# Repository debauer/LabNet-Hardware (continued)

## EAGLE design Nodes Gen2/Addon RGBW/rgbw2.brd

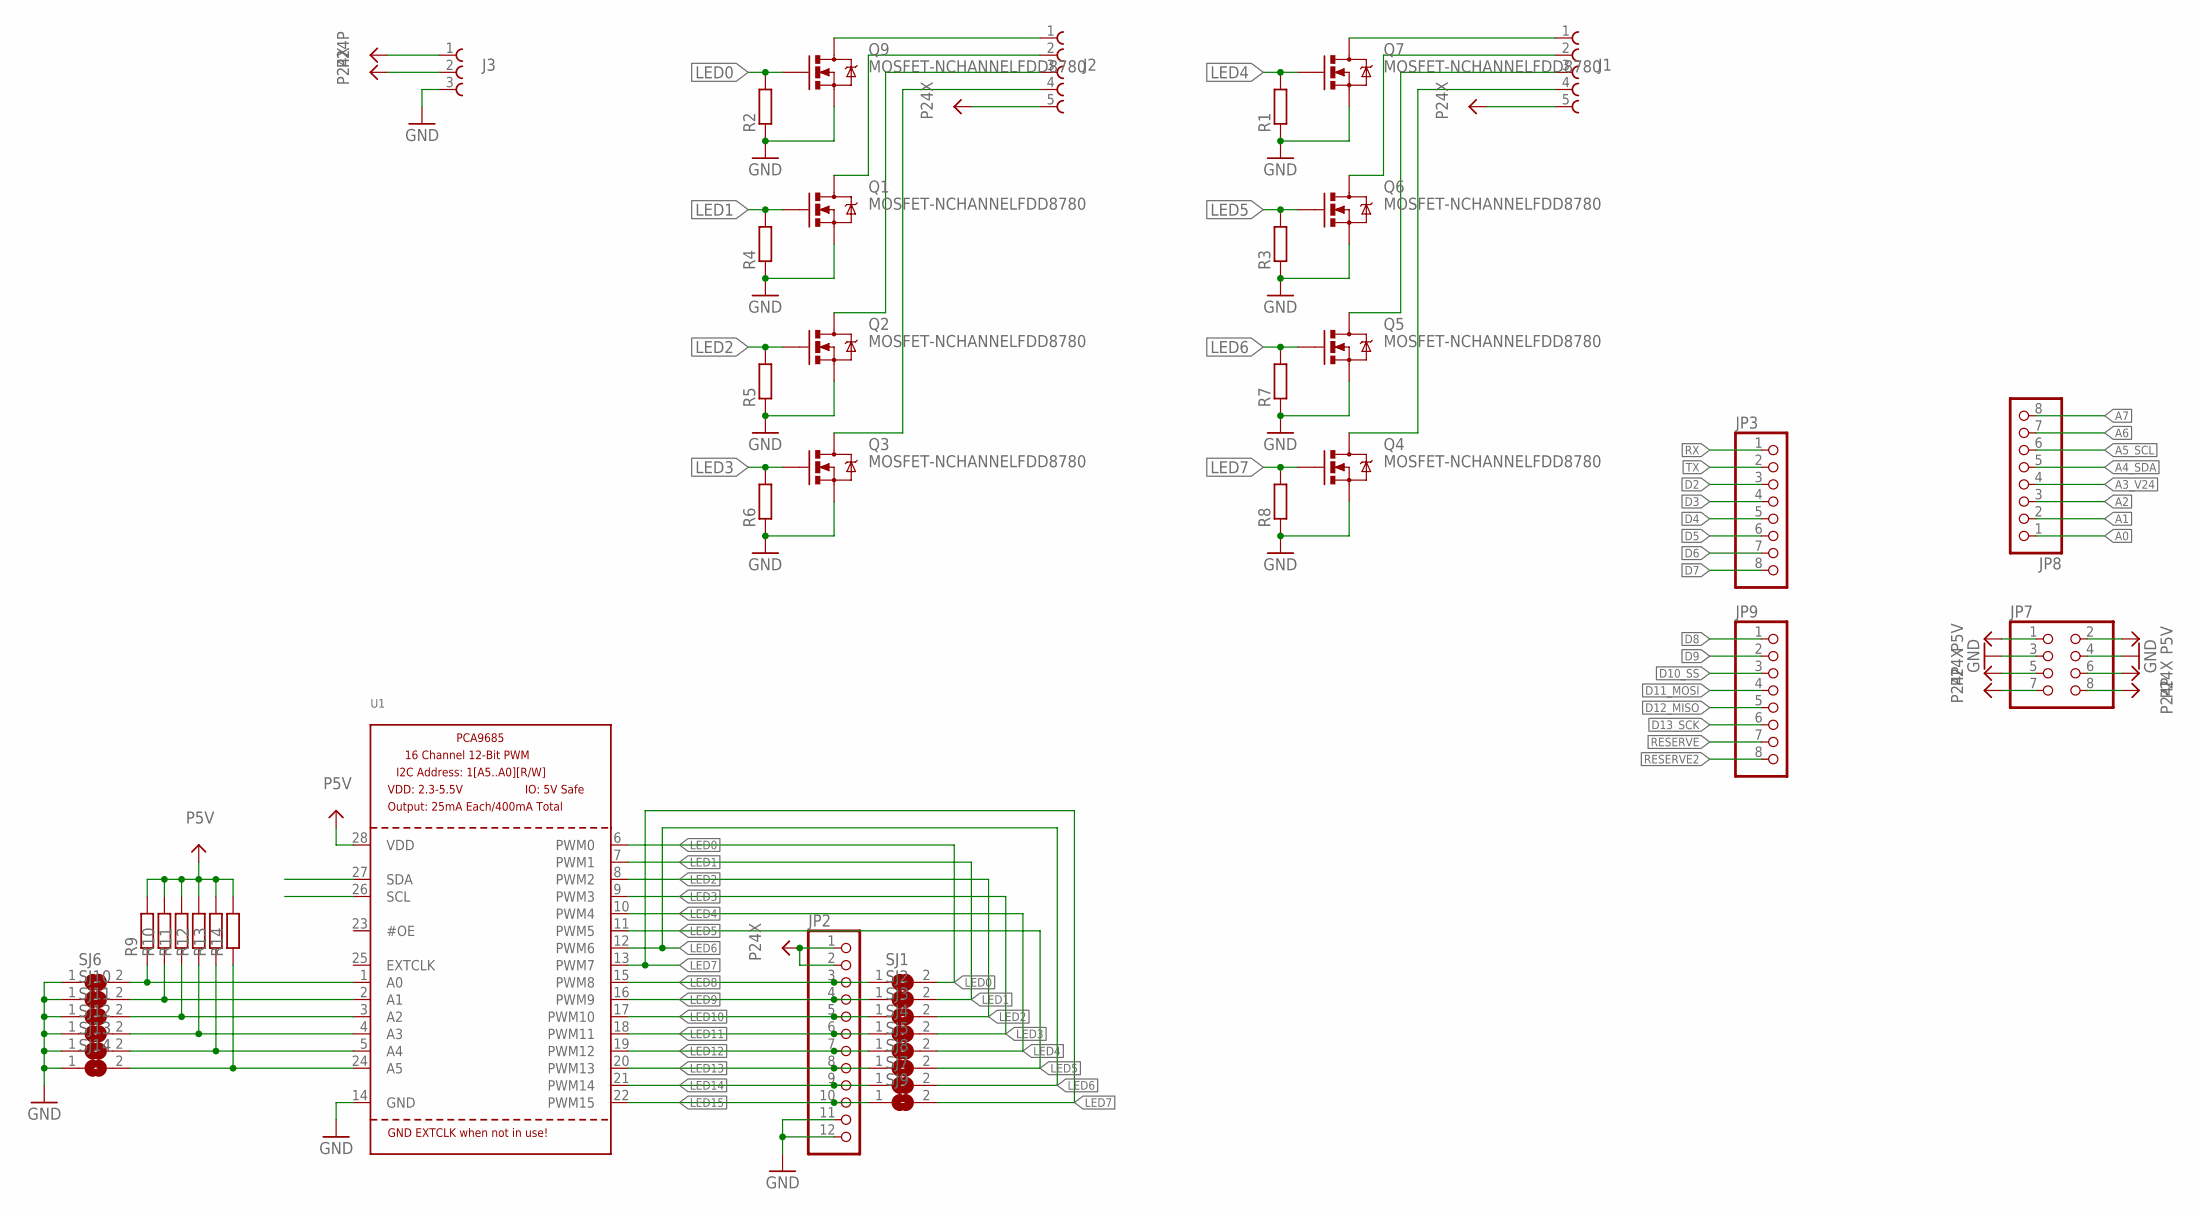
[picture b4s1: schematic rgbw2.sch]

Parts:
J1, J2: 691322310005
J3: 691313510003
JP2: PINHD-1X12; 1X12
JP3, JP8, JP9: PINHD-1X8; 1X08
JP7: PINHD-2X4; 2X04
Q1, Q2, Q3, Q4, Q5, Q6, Q7, Q9: MOSFET-NCHANNELFDD8780; DPAK
R1, R2, R3, R4, R5, R6, R7, R8, R9, R10, R11, R12, R13, R14: R-EU_R0805; R0805
SJ1, SJ2, SJ3, SJ4, SJ5, SJ6, SJ7, SJ8, SJ9, SJ10, SJ11, SJ12, SJ13, SJ14: SJN; SJ
U1: PCA9685; TSSOP28

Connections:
A0: JP8.1
A1: JP8.2
A2: JP8.3
A3_V24: JP8.4
A4_SDA: JP8.5, U1.27 (SDA)
A5_SCL: JP8.6, U1.26 (SCL)
A6: JP8.7
A7: JP8.8
D2: JP3.3
D3: JP3.4
D4: JP3.5
D5: JP3.6
D6: JP3.7
D7: JP3.8
D8: JP9.1
D9: JP9.2
D10_SS: JP9.3
D11_MOSI: JP9.4
D12_MISO: JP9.5
D13_SCK: JP9.6
GND: J3.3, JP2.11, JP2.12, JP7.3, JP7.4, Q1.3 (S), Q2.3 (S), Q3.3 (S), Q4.3 (S), Q5.3 (S), Q6.3 (S), Q7.3 (S), Q9.3 (S), R1.1, R2.1, R3.1, R4.1, R5.1, R6.1, R7.1, R8.1, SJ6.1, SJ10.1, SJ11.1, SJ12.1, SJ13.1, SJ14.1, U1.14 (GND)
LED0: Q9.1 (G), R2.2, SJ1.2, U1.6 (PWM0)
LED1: Q1.1 (G), R4.2, SJ2.2, U1.7 (PWM1)
LED2: Q2.1 (G), R5.2, SJ3.2, U1.8 (PWM2)
LED3: Q3.1 (G), R6.2, SJ4.2, U1.9 (PWM3)
LED4: Q7.1 (G), R1.2, SJ5.2, U1.10 (PWM4)
LED5: Q6.1 (G), R3.2, SJ8.2, U1.11 (PWM5)
LED6: Q5.1 (G), R7.2, SJ7.2, U1.12 (PWM6)
LED7: Q4.1 (G), R8.2, SJ9.2, U1.13 (PWM7)
LED8: JP2.3, SJ1.1, U1.15 (PWM8)
LED9: JP2.4, SJ2.1, U1.16 (PWM9)
LED10: JP2.5, SJ3.1, U1.17 (PWM10)
LED11: JP2.6, SJ4.1, U1.18 (PWM11)
LED12: JP2.7, SJ5.1, U1.19 (PWM12)
LED13: JP2.8, SJ8.1, U1.20 (PWM13)
LED14: JP2.9, SJ7.1, U1.21 (PWM14)
LED15: JP2.10, SJ9.1, U1.22 (PWM15)
unnamed: R9.1, SJ6.2, U1.1 (A0)
unnamed: J2.1, Q9.4 (D)
unnamed: J2.2, Q1.4 (D)
unnamed: J1.3, Q5.4 (D)
unnamed: J2.3, Q2.4 (D)
unnamed: J2.4, Q3.4 (D)
unnamed: J1.4, Q4.4 (D)
unnamed: J1.1, Q7.4 (D)
unnamed: J1.2, Q6.4 (D)
unnamed: R10.1, SJ10.2, U1.2 (A1)
unnamed: R11.1, SJ11.2, U1.3 (A2)
unnamed: R12.1, SJ12.2, U1.4 (A3)
unnamed: R13.1, SJ13.2, U1.5 (A4)
unnamed: R14.1, SJ14.2, U1.24 (A5)
P5V: JP7.1, JP7.2, R9.2, R10.2, R11.2, R12.2, R13.2, R14.2, U1.28 (VDD)
P24P: J3.1, JP7.7, JP7.8
P24X: J1.5, J2.5, J3.2, JP2.1, JP2.2, JP7.5, JP7.6
RESERVE: JP9.7
RESERVE2: JP9.8
RX: JP3.1
TX: JP3.2

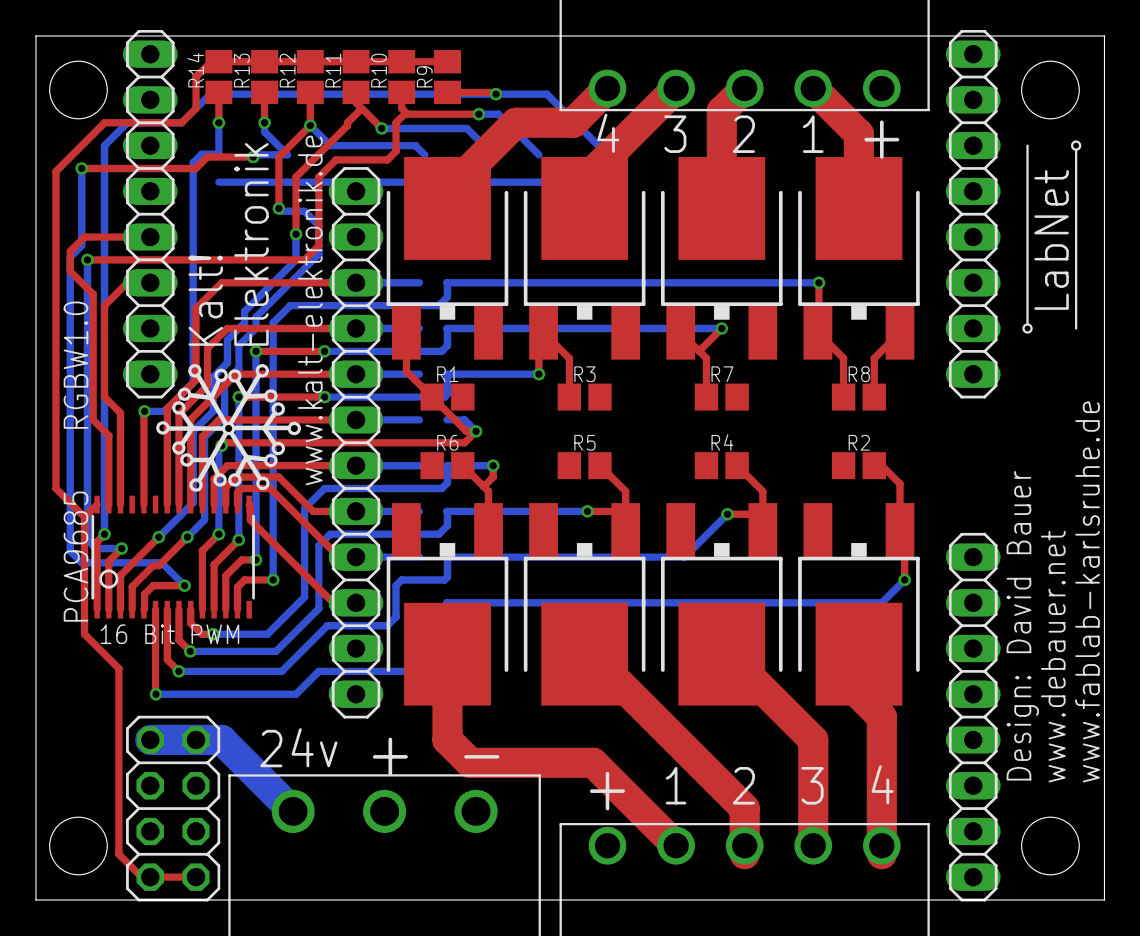
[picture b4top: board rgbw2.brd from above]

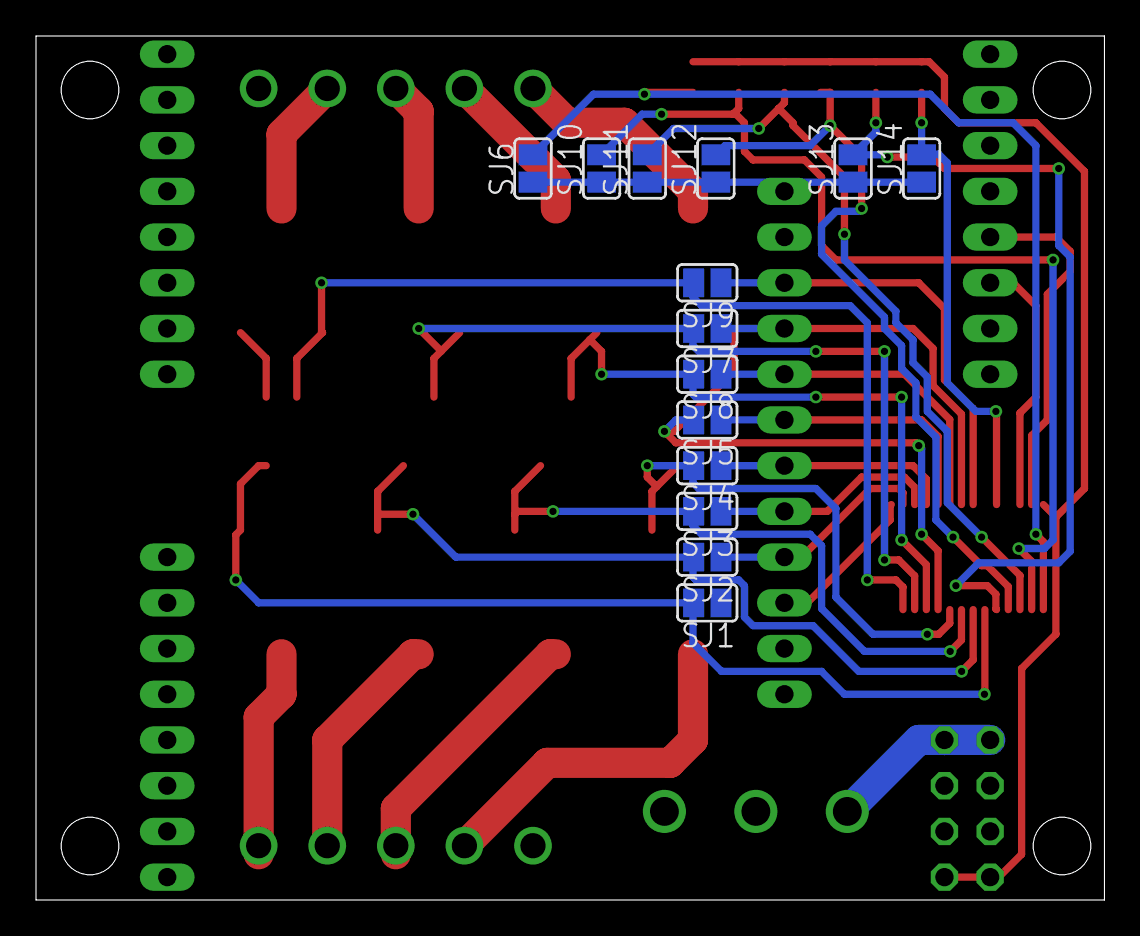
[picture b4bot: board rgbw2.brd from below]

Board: 2 copper layers, 59.4 x 48.0 mm, 47 parts (14 on the bottom side), 36 nets.

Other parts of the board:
U$1: KALT!ELEKTRONIK
U$2: LABNET

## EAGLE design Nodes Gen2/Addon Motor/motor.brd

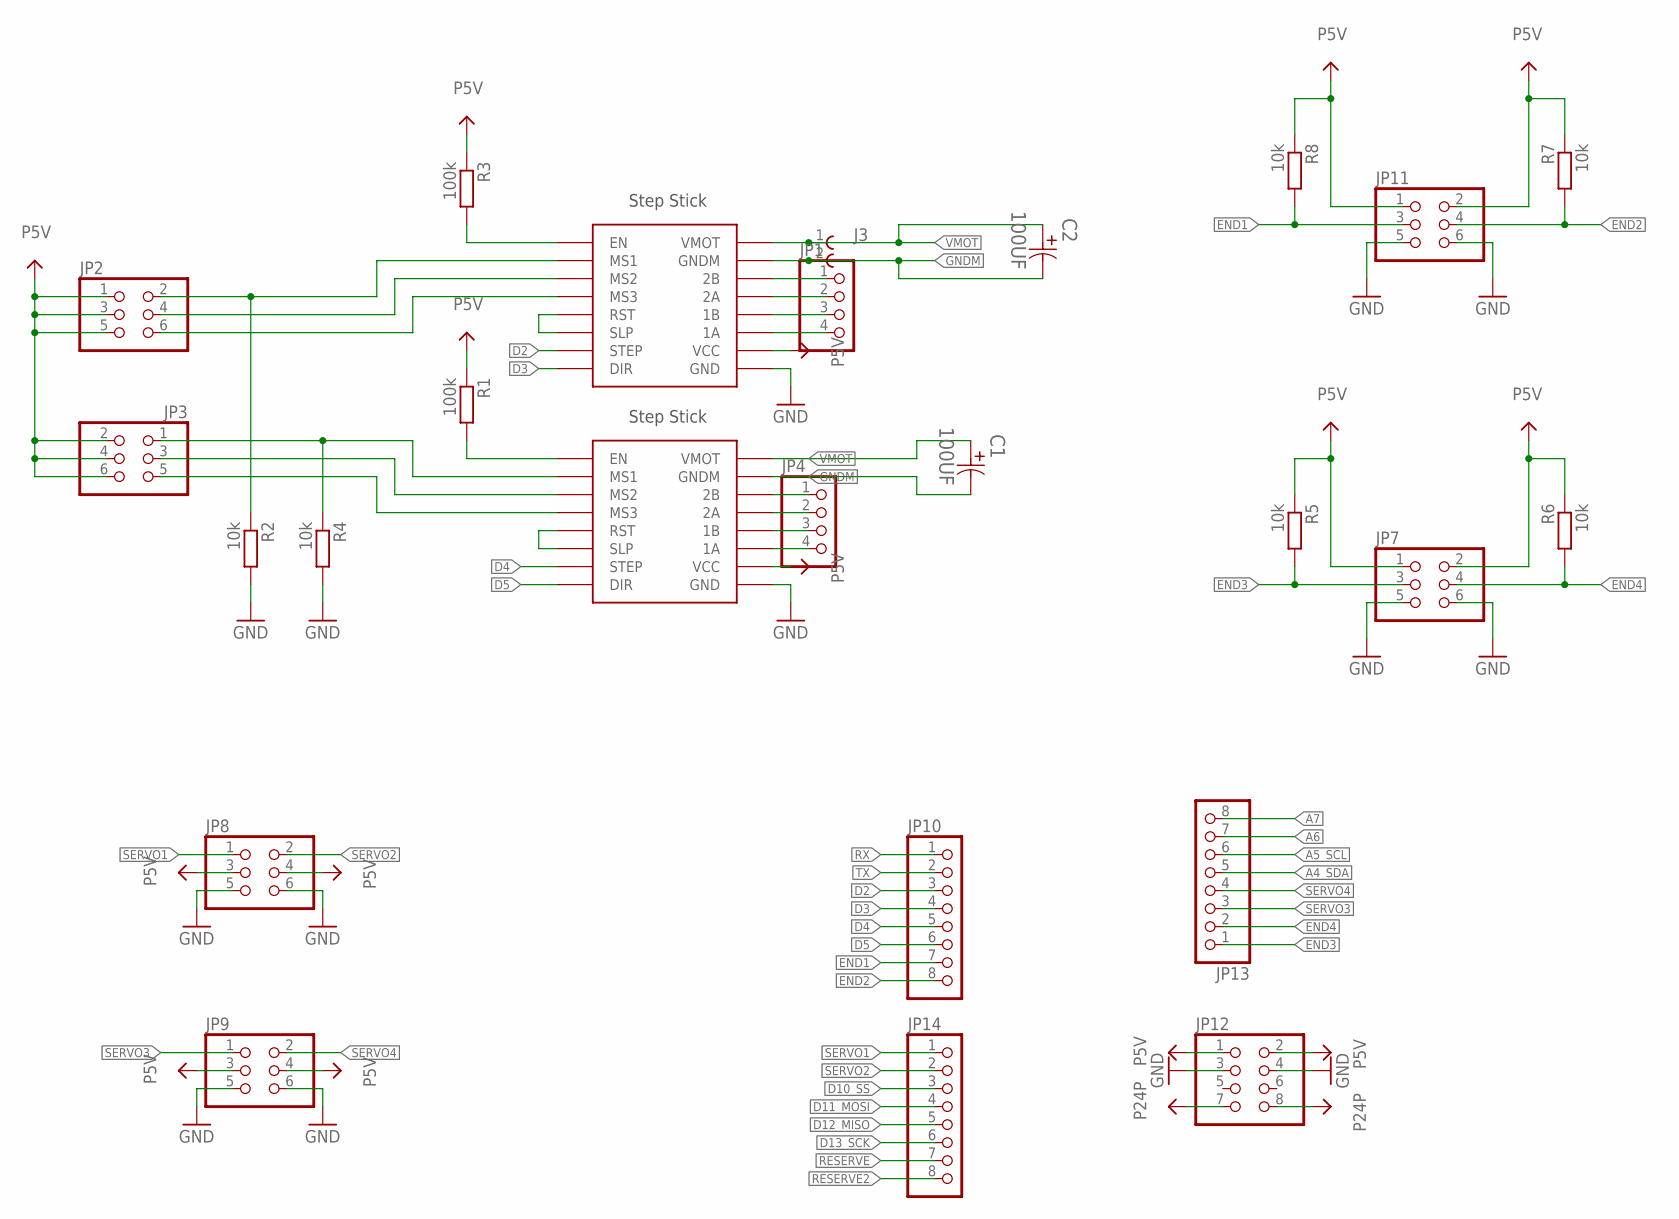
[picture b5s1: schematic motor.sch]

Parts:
C1, C2: 100UF; CAPAE830X1050N
J3: 691312510002
JP1, JP4: PINHD-1X4/90; 1X04/90
JP2, JP3: PINHD-2X3; 2X03
JP7, JP8, JP9, JP11: PINHD-2X3/90; 2X03/90
JP10, JP13, JP14: PINHD-1X8; 1X08
JP12: PINHD-2X4; 2X04
R1, R3: 100k; R0805
R2, R4, R5, R6, R7, R8: 10k; R0805
U$1, U$2: STEP-STICK

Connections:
A4_SDA: JP13.5
A5_SCL: JP13.6
A6: JP13.7
A7: JP13.8
D2: JP10.3, U$2.SPT (STEP)
D3: JP10.4, U$2.DIR
D4: JP10.5, U$1.SPT (STEP)
D5: JP10.6, U$1.DIR
D10_SS: JP14.3
D11_MOSI: JP14.4
D12_MISO: JP14.5
D13_SCK: JP14.6
END1: JP10.7, JP11.3, R8.2
END2: JP10.8, JP11.4, R7.2
END3: JP7.3, JP13.1, R5.2
END4: JP7.4, JP13.2, R6.2
GND: JP7.5, JP7.6, JP8.5, JP8.6, JP9.5, JP9.6, JP11.5, JP11.6, JP12.3, JP12.4, R2.2, R4.2, U$1.GND, U$2.GND
GNDM: C1.2, C2.2, J3.2, U$1.GNDM, U$2.GNDM
unnamed: JP2.2, R2.1, U$2.MS1
unnamed: JP2.4, U$2.MS2
unnamed: JP2.6, U$2.MS3
unnamed: JP3.1, R4.1, U$1.MS1
unnamed: JP3.3, U$1.MS2
unnamed: JP3.5, U$1.MS3
unnamed: R1.2, U$1.EN
unnamed: U$2.RST, U$2.SLP
unnamed: R3.2, U$2.EN
unnamed: U$1.RST, U$1.SLP
unnamed: JP1.4, U$2.1A
unnamed: JP1.3, U$2.1B
unnamed: JP1.2, U$2.2A
unnamed: JP1.1, U$2.2B
unnamed: JP4.1, U$1.2B
unnamed: JP4.2, U$1.2A
unnamed: JP4.3, U$1.1B
unnamed: JP4.4, U$1.1A
P5V: JP2.1, JP2.3, JP2.5, JP3.2, JP3.4, JP3.6, JP7.1, JP7.2, JP8.3, JP8.4, JP9.3, JP9.4, JP11.1, JP11.2, JP12.1, JP12.2, R1.1, R3.1, R5.1, R6.1, R7.1, R8.1, U$1.VCC, U$2.VCC
P24P: JP12.7, JP12.8
RESERVE: JP14.7
RESERVE2: JP14.8
RX: JP10.1
SERVO1: JP8.1, JP14.1
SERVO2: JP8.2, JP14.2
SERVO3: JP9.1, JP13.3
SERVO4: JP9.2, JP13.4
TX: JP10.2
VMOT: C1.1, C2.1, J3.1, U$1.VMOT, U$2.VMOT

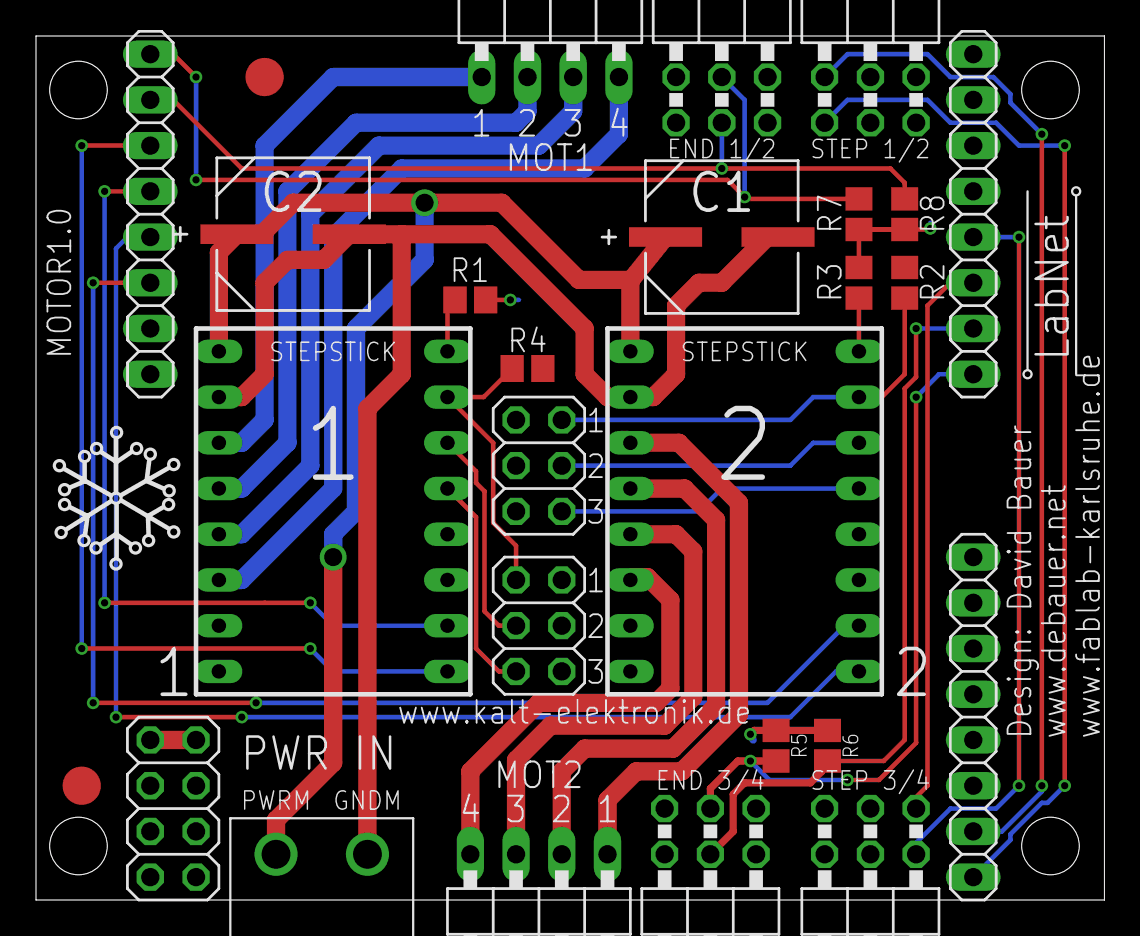
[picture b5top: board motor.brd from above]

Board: 2 copper layers, 59.4 x 48.0 mm, 30 parts (1 on the bottom side), 35 nets.

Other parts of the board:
U$3, U$8: PASSMARK
U$4: SNOW
U$6: KALT!ELEKTRONIK
U$7: LABNET

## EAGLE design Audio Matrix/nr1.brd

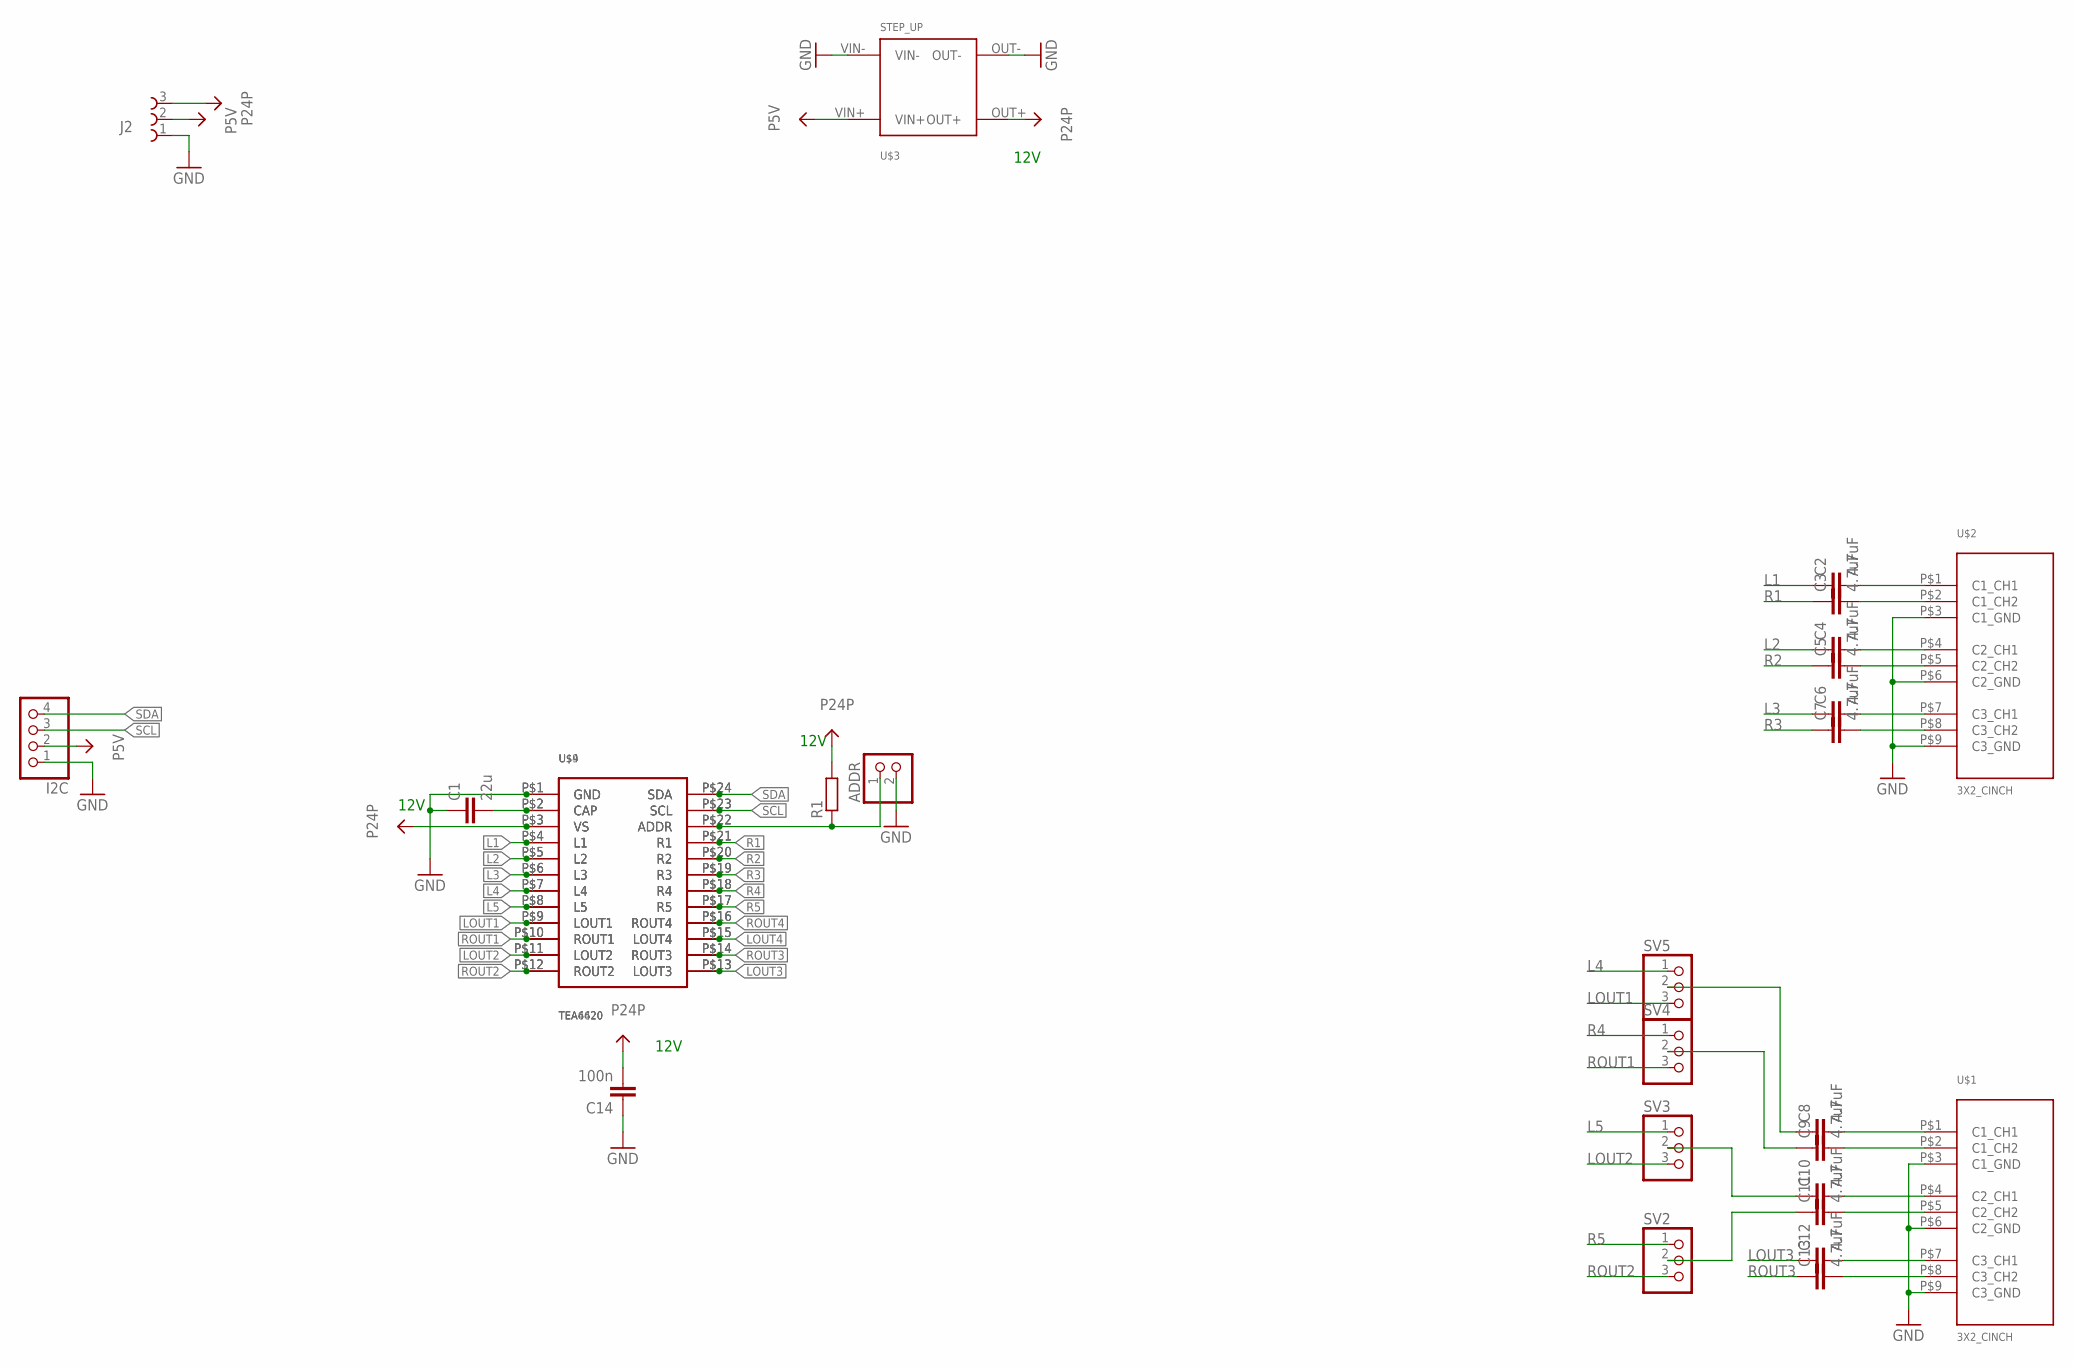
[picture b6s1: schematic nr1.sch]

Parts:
ADDR: PINHD-1X2; 1X02
C1: 22u; C0805
C2, C3, C4, C5, C6, C7, C8, C9, C10, C11, C12, C13: 4.7uF; C0805
C14: 100n; C0805
I2C: PINHD-1X4; 1X04
J2: 691210910003
R1: R-EU_R0805; R0805
SV2, SV3, SV4, SV5: PINHD-1X3; 1X03
U$1, U$2: 3X2_CINCH
U$3: STEP_UP
U$4: TEA4620
U$9: TEA6420; SHRINK24

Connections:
GND: ADDR.2, C1.1, C14.1, I2C.1, J2.1, U$1.P$3 (C1_GND), U$1.P$6 (C2_GND), U$1.P$9 (C3_GND), U$2.P$3 (C1_GND), U$2.P$6 (C2_GND), U$2.P$9 (C3_GND), U$3.OUT-, U$3.VIN-, U$4.P$1 (GND), U$9.P$1 (GND)
L1: C2.1, U$4.P$4 (L1), U$9.P$4 (L1)
L2: C4.1, U$4.P$5 (L2), U$9.P$5 (L2)
L3: C6.1, U$4.P$6 (L3), U$9.P$6 (L3)
L4: SV5.1, U$4.P$7 (L4), U$9.P$7 (L4)
L5: SV3.1, U$4.P$8 (L5), U$9.P$8 (L5)
LOUT1: SV5.3, U$4.P$9 (LOUT1), U$9.P$9 (LOUT1)
LOUT2: SV3.3, U$4.P$11 (LOUT2), U$9.P$11 (LOUT2)
LOUT3: C12.1, U$4.P$13 (LOUT3), U$9.P$13 (LOUT3)
LOUT4: U$4.P$15 (LOUT4), U$9.P$15 (LOUT4)
unnamed: C8.1, SV5.2
unnamed: C9.1, SV4.2
unnamed: ADDR.1, R1.1, U$4.P$22 (ADDR), U$9.P$22 (ADDR)
unnamed: C1.2, U$4.P$2 (CAP), U$9.P$2 (CAP)
unnamed: C10.1, SV3.2
unnamed: C11.1, SV2.2
unnamed: C2.2, U$2.P$1 (C1_CH1)
unnamed: C3.2, U$2.P$2 (C1_CH2)
unnamed: C4.2, U$2.P$4 (C2_CH1)
unnamed: C5.2, U$2.P$5 (C2_CH2)
unnamed: C6.2, U$2.P$7 (C3_CH1)
unnamed: C7.2, U$2.P$8 (C3_CH2)
unnamed: C8.2, U$1.P$1 (C1_CH1)
unnamed: C9.2, U$1.P$2 (C1_CH2)
unnamed: C10.2, U$1.P$4 (C2_CH1)
unnamed: C11.2, U$1.P$5 (C2_CH2)
unnamed: C12.2, U$1.P$7 (C3_CH1)
unnamed: C13.2, U$1.P$8 (C3_CH2)
P5V: I2C.2, J2.2, U$3.VIN+
P24P: C14.2, J2.3, R1.2, U$3.OUT+, U$4.P$3 (VS), U$9.P$3 (VS)
R1: C3.1, U$4.P$21 (R1), U$9.P$21 (R1)
R2: C5.1, U$4.P$20 (R2), U$9.P$20 (R2)
R3: C7.1, U$4.P$19 (R3), U$9.P$19 (R3)
R4: SV4.1, U$4.P$18 (R4), U$9.P$18 (R4)
R5: SV2.1, U$4.P$17 (R5), U$9.P$17 (R5)
ROUT1: SV4.3, U$4.P$10 (ROUT1), U$9.P$10 (ROUT1)
ROUT2: SV2.3, U$4.P$12 (ROUT2), U$9.P$12 (ROUT2)
ROUT3: C13.1, U$4.P$14 (ROUT3), U$9.P$14 (ROUT3)
ROUT4: U$4.P$16 (ROUT4), U$9.P$16 (ROUT4)
SCL: I2C.3, U$4.P$23 (SCL), U$9.P$23 (SCL)
SDA: I2C.4, U$4.P$24 (SDA), U$9.P$24 (SDA)

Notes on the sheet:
12V

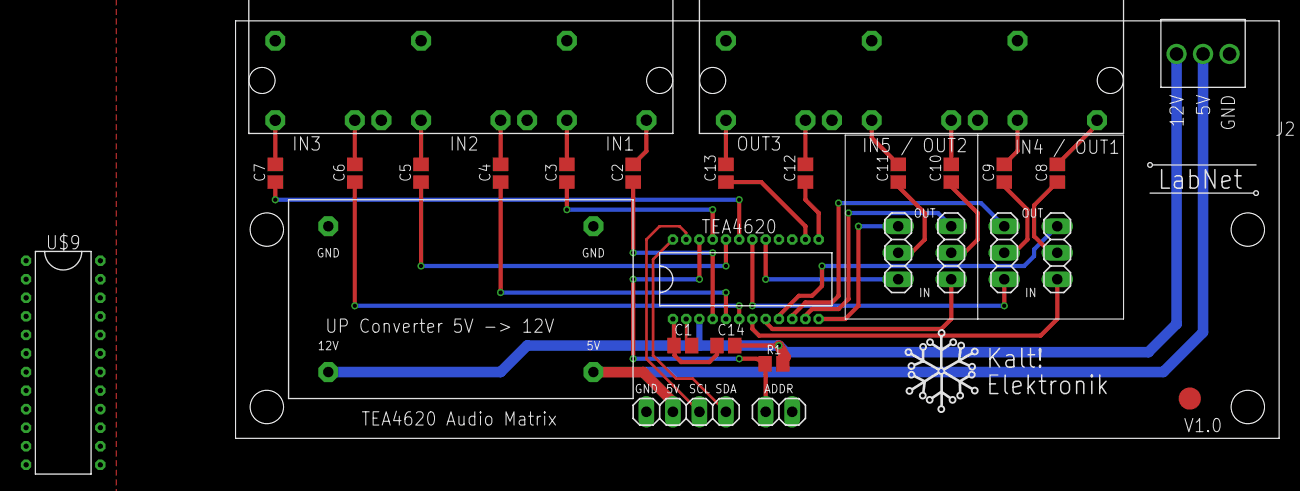
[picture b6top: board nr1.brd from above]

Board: 2 copper layers, 100.0 x 40.0 mm, 30 parts (0 on the bottom side), 41 nets.

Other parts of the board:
U$6: PASSMARK
U$7: LABNET
U$8: KALT!ELEKTRONIK

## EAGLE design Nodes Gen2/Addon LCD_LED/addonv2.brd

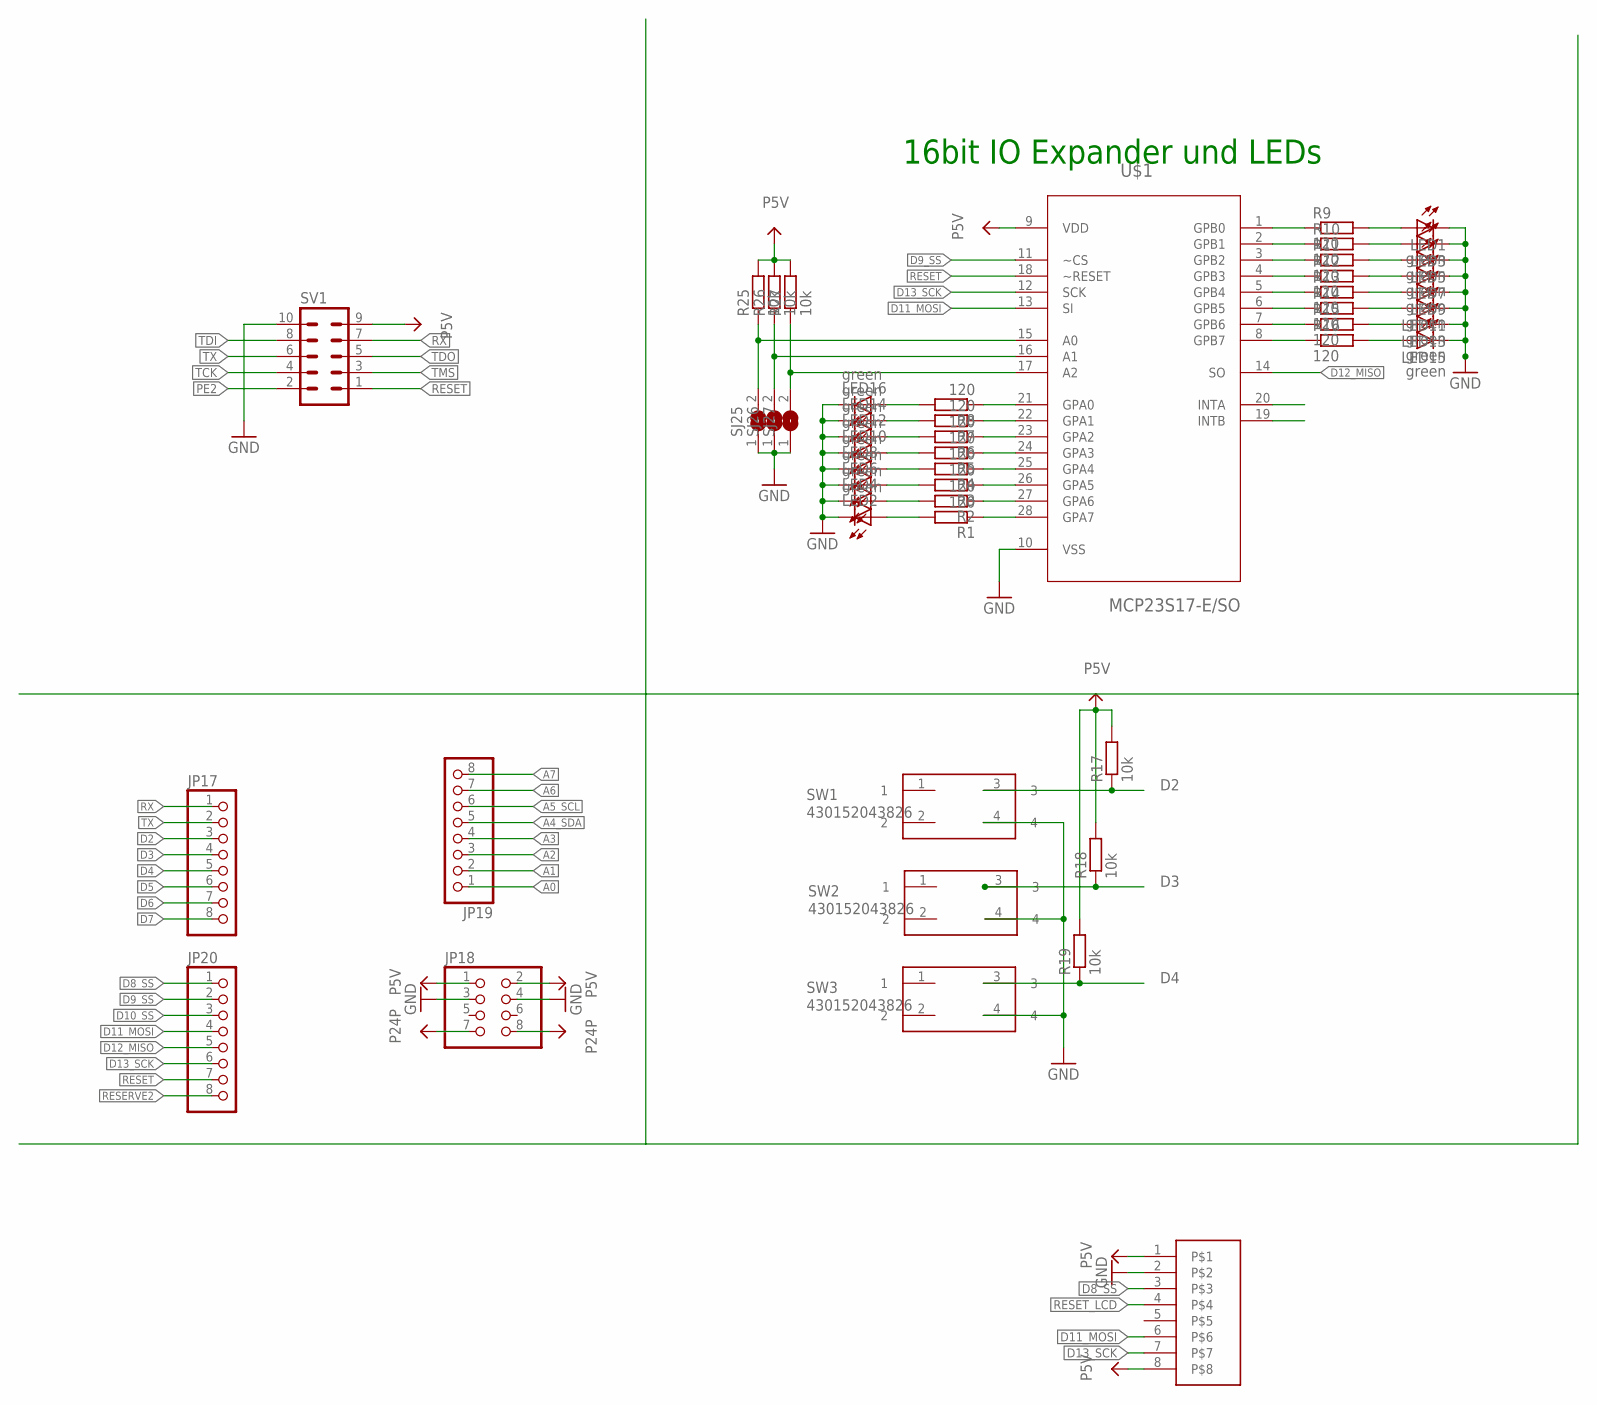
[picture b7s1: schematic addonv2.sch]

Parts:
JP17, JP19, JP20: PINHD-1X8; 1X08
JP18: PINHD-2X4; 2X04
LED1, LED2, LED3, LED4, LED5, LED6, LED7, LED8, LED9, LED10, LED11, LED12, LED13, LED14, LED15, LED16: green; CHIPLED_0805
R1, R2, R3, R4, R5, R6, R7, R8, R9, R10, R11, R12, R13, R14, R15, R16: 120; R0805
R17, R18, R19, R25, R26, R27: 10k; R0805
SJ25, SJ26, SJ27: SJN; SJ
SV1: ML10L
SW1, SW2, SW3: 430152043826
U$1: MCP23S17-E/SO; SOIC127P030X265-28N
U$3: 1.44-128X128

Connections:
A0: JP19.1
A1: JP19.2
A2: JP19.3
A3: JP19.4
A4_SDA: JP19.5
A5_SCL: JP19.6
A6: JP19.7
A7: JP19.8
D2: JP17.3, R17.1, SW1.3
D3: JP17.4, R18.1, SW2.3
D4: JP17.5, R19.1, SW3.3
D5: JP17.6
D6: JP17.7
D7: JP17.8
D8_SS: JP20.1, U$3.3
D9_SS: JP20.2, U$1.11 (~CS)
D10_SS: JP20.3
D11_MOSI: JP20.4, U$1.13 (SI), U$3.6
D12_MISO: JP20.5, U$1.14 (SO)
D13_SCK: JP20.6, U$1.12 (SCK), U$3.7
GND: JP18.3, JP18.4, LED1.C, LED2.C, LED3.C, LED4.C, LED5.C, LED6.C, LED7.C, LED8.C, LED9.C, LED10.C, LED11.C, LED12.C, LED13.C, LED14.C, LED15.C, LED16.C, SJ25.1, SJ26.1, SJ27.1, SV1.10, SW1.4, SW2.4, SW3.4, U$1.10 (VSS), U$3.2
unnamed: LED1.A, R9.2
unnamed: LED3.A, R10.2
unnamed: LED5.A, R11.2
unnamed: LED7.A, R12.2
unnamed: LED9.A, R13.2
unnamed: LED11.A, R14.2
unnamed: LED13.A, R15.2
unnamed: LED15.A, R16.2
unnamed: R9.1, U$1.1 (GPB0)
unnamed: R10.1, U$1.2 (GPB1)
unnamed: R11.1, U$1.3 (GPB2)
unnamed: R12.1, U$1.4 (GPB3)
unnamed: R13.1, U$1.5 (GPB4)
unnamed: R14.1, U$1.6 (GPB5)
unnamed: R15.1, U$1.7 (GPB6)
unnamed: R16.1, U$1.8 (GPB7)
unnamed: LED2.A, R1.2
unnamed: LED4.A, R2.2
unnamed: LED6.A, R3.2
unnamed: LED8.A, R4.2
unnamed: LED10.A, R5.2
unnamed: LED12.A, R6.2
unnamed: LED14.A, R7.2
unnamed: LED16.A, R8.2
unnamed: R1.1, U$1.28 (GPA7)
unnamed: R2.1, U$1.27 (GPA6)
unnamed: R3.1, U$1.26 (GPA5)
unnamed: R4.1, U$1.25 (GPA4)
unnamed: R5.1, U$1.24 (GPA3)
unnamed: R6.1, U$1.23 (GPA2)
unnamed: R7.1, U$1.22 (GPA1)
unnamed: R8.1, U$1.21 (GPA0)
unnamed: R25.1, SJ25.2, U$1.15 (A0)
unnamed: R26.1, SJ26.2, U$1.16 (A1)
unnamed: R27.1, SJ27.2, U$1.17 (A2)
P5V: JP18.1, JP18.2, R17.2, R18.2, R19.2, R25.2, R26.2, R27.2, SV1.9, U$1.9 (VDD), U$3.1, U$3.8
P24P: JP18.7, JP18.8
PE2: SV1.2
RESERVE2: JP20.8
RESET: JP20.7, SV1.1, U$1.18 (~RESET)
RESET_LCD: U$3.4
RX: JP17.1, SV1.7
TCK: SV1.4
TDI: SV1.8
TDO: SV1.5
TMS: SV1.3
TX: JP17.2, SV1.6

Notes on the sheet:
16bit IO Expander und LEDs

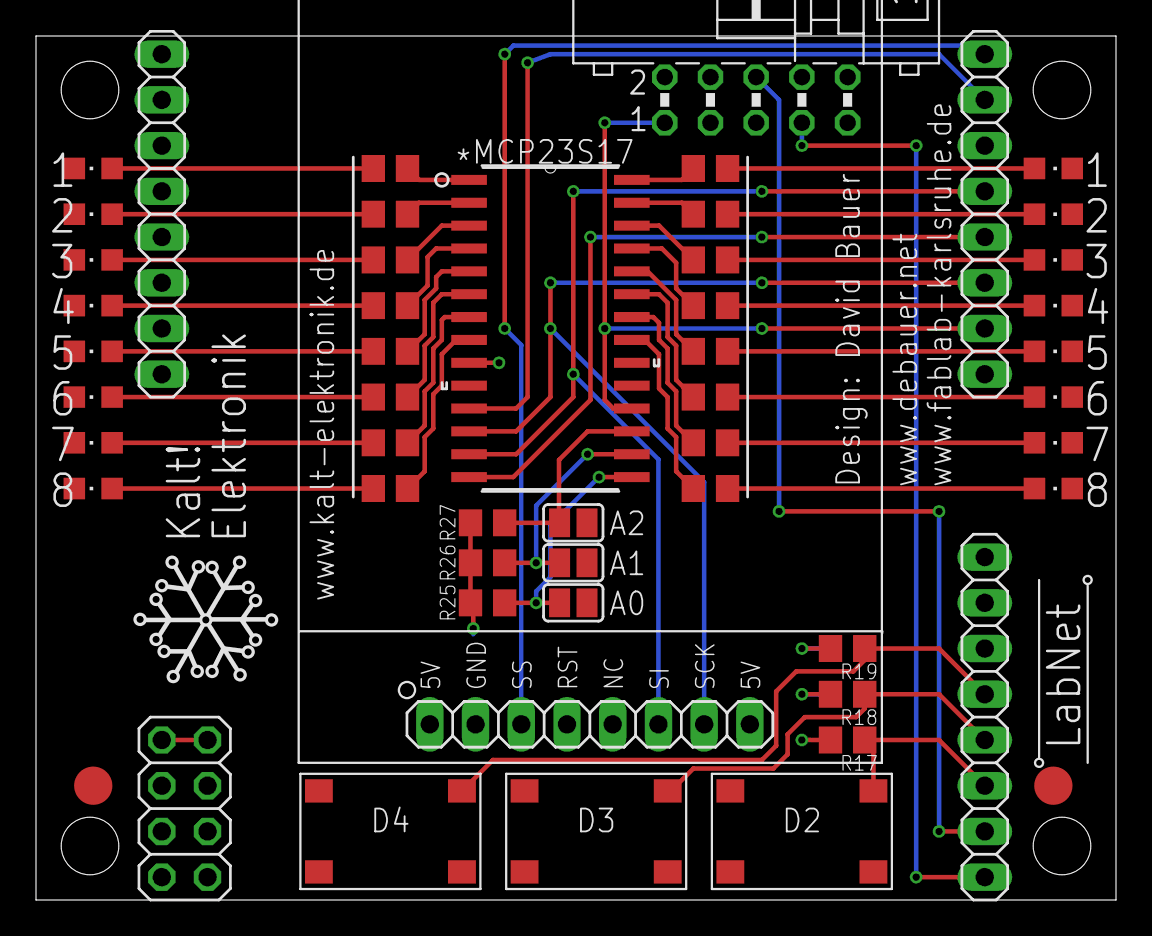
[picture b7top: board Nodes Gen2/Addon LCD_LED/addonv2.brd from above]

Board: 2 copper layers, 60.0 x 48.0 mm, 55 parts (0 on the bottom side), 49 nets.

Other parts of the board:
U$2: LABNET
U$4: KALT!ELEKTRONIK
U$5, U$7: PASSMARK

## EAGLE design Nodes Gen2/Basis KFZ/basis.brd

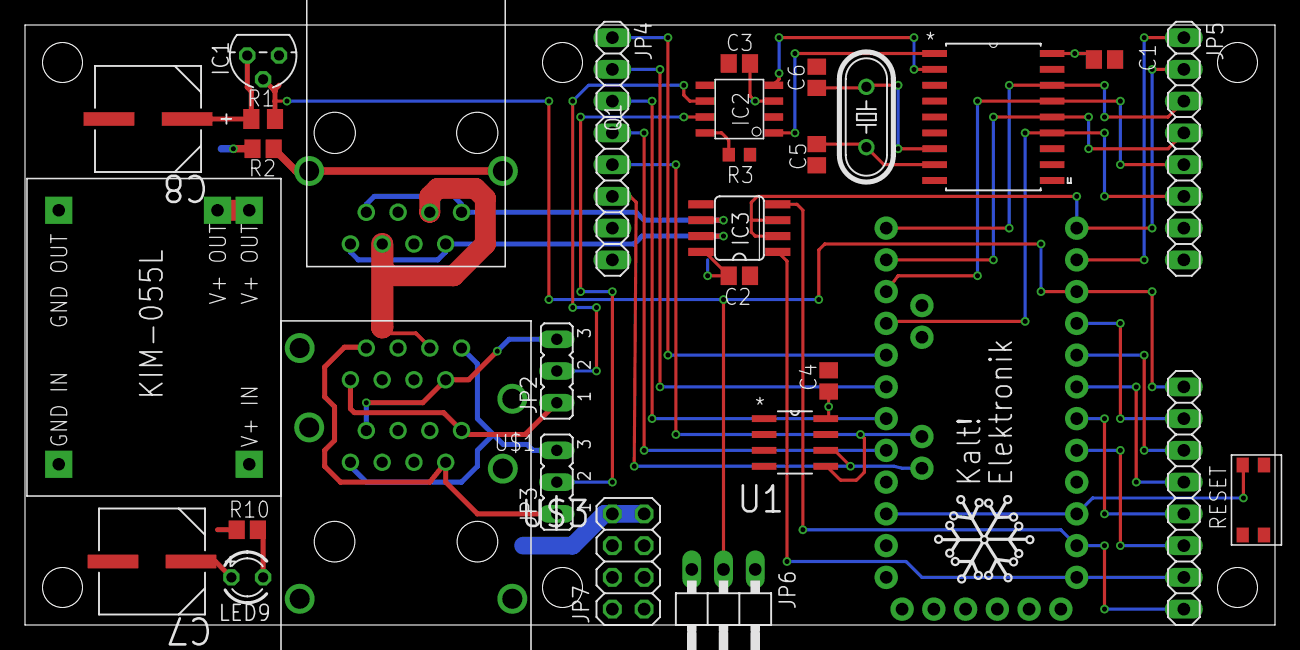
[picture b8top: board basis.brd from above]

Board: 2 copper layers, 100.0 x 48.0 mm, 33 parts (1 on the bottom side), 39 nets.

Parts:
C1, C2, C4: 100n; C0805
C3: C0805
C5, C6: 22p; C0805
C7, C8: 100UF; CAPAE830X1050N
CON1: MEBP
IC1: DS1820TO92; TO-92
IC2: MCP2551; SO-8
IC3: MAX481CSA; SO08
JP1, JP4, JP5: 1X08
JP2, JP3: JP2
JP6: 1X03/90
JP7: 2X04
K4: 615016240521
LED9: LED3MM
MOD1: KIM-055L
Q1: HC49/S
R1: 4k7; M0805
R2: 1M; R0805
R3: 10k; R0603
R10: 4k7; R0805
RESET: 434351045816
U1: AT24C64CN-SH-B; SOIC127P600X175-8N
U$1: ARDUINO_PRO_MINI
U$2, U$4: KALT!ELEKTRONIK
U$3: MCP2515-I/SO; SOIC127P1034X264-18N

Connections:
1W: IC1.2, JP1.8, JP6.2, R1.1, U$1.10
A0: JP4.1, U$1.17
A1: JP4.2, U$1.18
A2: JP4.3, U$1.19
A3: JP4.4, U$1.20
A4_SDA: JP4.5, U1.5, U$1.A4
A5_SCL: JP4.6, U1.6, U$1.A5
CANH: IC2.7, JP3.2
CANH1: JP3.3, K4.A1, K4.B1
CANH2: JP3.1, K4.A7, K4.B7
CANL: IC2.6, JP2.2
CANL1: JP2.3, K4.A2, K4.B2
CANL2: JP2.1, K4.A8, K4.B8
CANRX: IC2.4, U$3.2
CANTX: IC2.1, U$3.1
D2: JP1.3, U$1.5
D3: JP1.4, U$1.6
D4: JP1.5, U$1.7
D5: JP1.6, U$1.8
D6: JP1.7, U$1.9
D8_SS: JP5.1, U$1.11
D9_SS: IC3.2, IC3.3, JP5.2, U$1.12
D10_SS: JP5.3, U$1.13, U$3.16
D11_MOSI: JP5.4, U$1.14, U$3.14
D12_MISO: JP5.5, U$1.15, U$3.15
D13_SCK: JP5.6, U$1.16, U$3.13
GND: C1.2, C2.2, C3.2, C4.2, C5.2, C6.2, C7.2, C8.2, CON1.4, CON1.5, IC1.1, IC2.2, IC3.5, JP6.3, JP7.3, JP7.4, K4.A4, K4.A5, K4.B4, K4.B5, MOD1.GNDIN, MOD1.GNDOUT, R2.1, R3.2, R10.1, RESET.2, U1.1, U1.2, U1.3, U1.4, U1.7, U$1.4, U$1.23, U$3.9
MCP_OSC1: C5.1, Q1.1, U$3.8
MCP_OSC2: C6.1, Q1.2, U$3.7
unnamed: IC2.8, R3.1
unnamed: CON1.T1, CON1.T2, R2.2
unnamed: LED9.K, R10.2
P5V: C1.1, C2.1, C3.1, C4.1, C8.1, IC1.3, IC2.3, IC3.8, JP6.1, JP7.1, JP7.2, MOD1.V+OUT1, MOD1.V+OUT2, R1.2, U1.8, U$1.21, U$3.18
P24P: C7.1, CON1.3, CON1.6, JP7.7, JP7.8, K4.A3, K4.A6, K4.B3, K4.B6, LED9.A, MOD1.V+IN
RESET: RESET.1, U$1.3, U$1.22
RS485_A: CON1.1, CON1.7, IC3.6
RS485_B: CON1.2, CON1.8, IC3.7
RX: IC3.4, JP1.1, U$1.2
TX: IC3.1, JP1.2, U$1.1

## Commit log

2015-03-18 init with v2 nodes
2015-03-18 labnet nodes mit 1206 als v2.1
2015-03-18 emBlocks Project startet und LED Blinkt - fuck yeah!
2015-03-19 iomodul2.1 weitere verbesserungen und auf 0805 runter
2015-06-18 board version 3 begonnen
2015-06-18 overview erstellt
2015-06-18 mod of CANable USB to CAN modul
2015-06-18 fixed board errors
2015-07-03 added readme and cleanup
2015-07-03 readme fix
2015-07-03 readme fix 2 - gruxefix nochmal!
2015-07-03 readme edit
2016-03-12 neue labnet nodes
2016-03-18 neue Platinen
2016-03-19 ordner umsortiert und module weiter gemacht
2016-03-20 motor addon
2016-03-21 laser addon
2016-03-24 gen 2 dev + bom
2016-03-25 bom updatet
2016-11-27 so much...
